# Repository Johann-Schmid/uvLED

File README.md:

# Project uvLED
## 3D Model of the pcb
 
## Pictures of the pcb 
 
## Pictures of the pcb with some UV-Leds
 
## Pictures of the pcb and the device

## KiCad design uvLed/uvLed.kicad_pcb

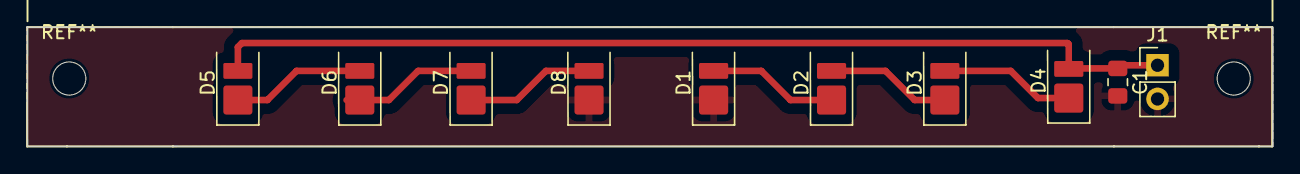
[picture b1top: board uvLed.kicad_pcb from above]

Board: 2 copper layers, 94.0 x 9.0 mm, 10 parts (0 on the bottom side), 8 nets.

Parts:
C1: 100n; C_0805_2012Metric_Pad1.18x1.45mm_HandSolder
D1, D2, D3, D4, D5, D6, D7, D8: LED; SMD-2
J1: Conn_01x02; PinHeader_1x02_P2.54mm_Vertical

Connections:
GND: C1.2, D1.1 (K), D8.1 (K), J1.2
unnamed: D1.2 (A), D2.1 (K)
unnamed: D2.2 (A), D3.1 (K)
unnamed: D3.2 (A), D4.1 (K)
unnamed: C1.1, D4.2 (A), D5.2 (A), J1.1
unnamed: D5.1 (K), D6.2 (A)
unnamed: D6.1 (K), D7.2 (A)
unnamed: D7.1 (K), D8.2 (A)

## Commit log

2024-01-08 schematic
2024-01-08 insert C
2024-01-12 change pcb
2024-01-12 insert JPG
2024-01-16 Insert dimension
2024-01-24 update pcb
2024-01-26 pictures
2024-02-06 arduino program
2024-02-06 insert file
